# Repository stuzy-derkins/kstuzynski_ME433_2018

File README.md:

Kristen Stuzynski
4/8/2018
This repository has everything I'm learning in 433!
Adding another line to Sync...

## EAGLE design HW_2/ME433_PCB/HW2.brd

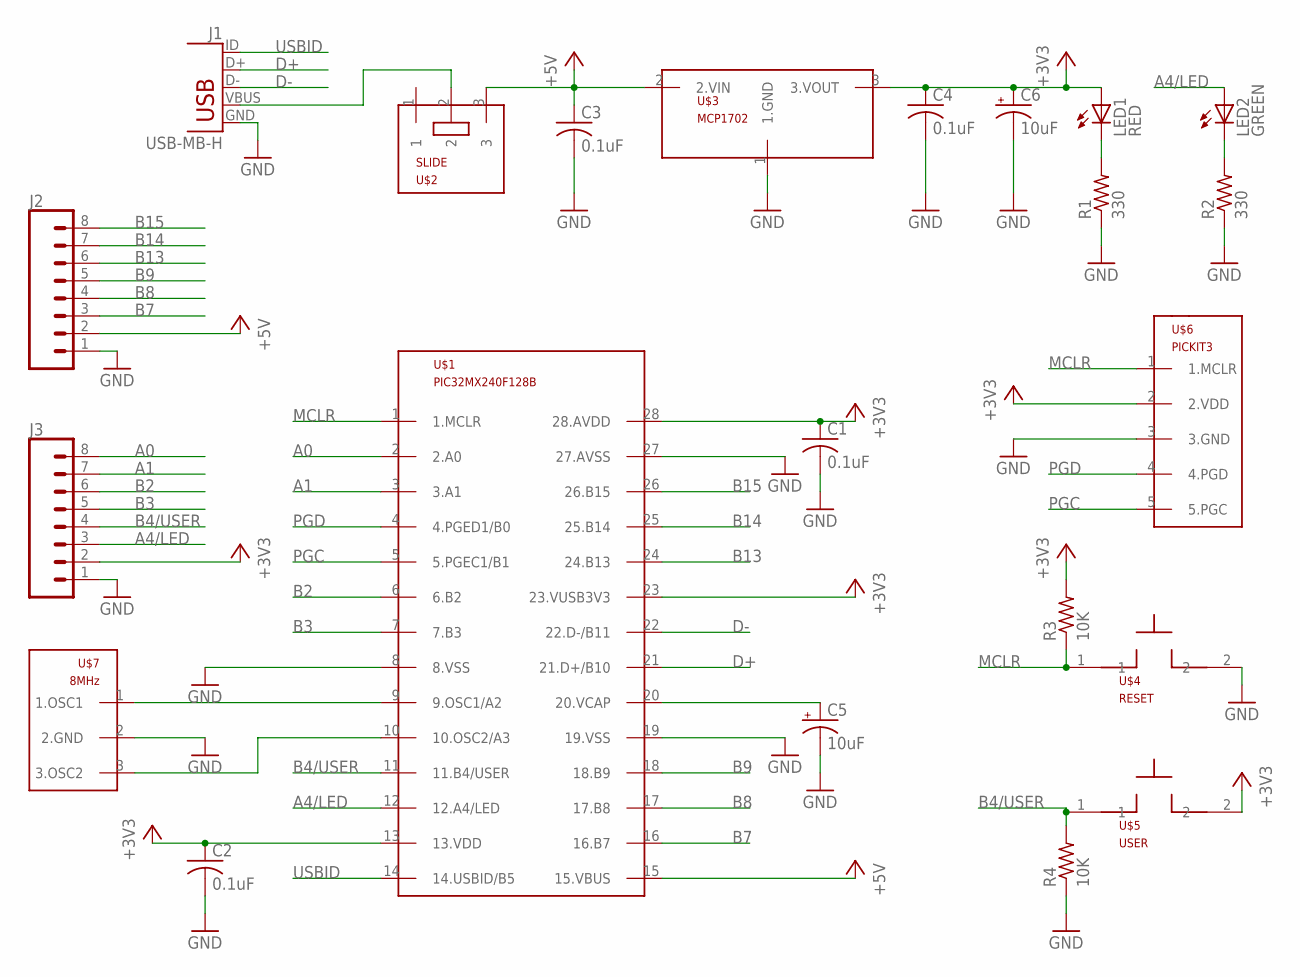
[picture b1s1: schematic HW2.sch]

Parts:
C1, C2, C3, C4: 0.1uF; C025-025X050
C5, C6: 10uF; B45181B
J1: USB-MB-H
J2, J3: CONN_08"; 1X08
LED1: RED; LED3MM
LED2: GREEN; LED3MM
R1, R2: 330; 0207/10
R3, R4: 10K; 0207/10
U$1: PIC32MX240F128B; DIL28-3
U$2: SLIDE
U$3: MCP1702; TO92
U$4: RESET; PUSHBUTTON
U$5: USER; PUSHBUTTON
U$6: PICKIT3; 1X05
U$7: 8MHz; OSC

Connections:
+3V3: C1.1, C2.1, C4.1, C6.+, J3.2, LED1.A, R3.2, U$1.13 (13.VDD), U$1.23 (23.VUSB3V3), U$1.28 (28.AVDD), U$3.3 (3.VOUT), U$5.2, U$6.2 (2.VDD)
+5V: C3.1, J2.2, U$1.15 (15.VBUS), U$2.3, U$3.2 (2.VIN)
A0: J3.8, U$1.2 (2.A0)
A1: J3.7, U$1.3 (3.A1)
A4/LED: J3.3, LED2.A, U$1.12 (12.A4/LED)
B2: J3.6, U$1.6 (6.B2)
B3: J3.5, U$1.7 (7.B3)
B4/USER: J3.4, R4.2, U$1.11 (11.B4/USER), U$5.1
B7: J2.3, U$1.16 (16.B7)
B8: J2.4, U$1.17 (17.B8)
B9: J2.5, U$1.18 (18.B9)
B13: J2.6, U$1.24 (24.B13)
B14: J2.7, U$1.25 (25.B14)
B15: J2.8, U$1.26 (26.B15)
D+: J1.D+, U$1.21 (21.D+/B10)
D-: J1.D-, U$1.22 (22.D-/B11)
GND: C1.2, C2.2, C3.2, C4.2, C5.-, C6.-, J1.GND, J2.1, J3.1, R1.1, R2.1, R4.1, U$1.8 (8.VSS), U$1.19 (19.VSS), U$1.27 (27.AVSS), U$3.1 (1.GND), U$4.2, U$6.3 (3.GND), U$7.2 (2.GND)
MCLR: R3.1, U$1.1 (1.MCLR), U$4.1, U$6.1 (1.MCLR)
unnamed: J1.VBUS, U$2.2
unnamed: LED1.K (C), R1.2
unnamed: U$1.9 (9.OSC1/A2), U$7.1 (1.OSC1)
unnamed: U$1.10 (10.OSC2/A3), U$7.3 (3.OSC2)
unnamed: C5.+, U$1.20 (20.VCAP)
unnamed: LED2.K (C), R2.2
PGC: U$1.5 (5.PGEC1/B1), U$6.5 (5.PGC)
PGD: U$1.4 (4.PGED1/B0), U$6.4 (4.PGD)
USBID: J1.ID, U$1.14 (14.USBID/B5)

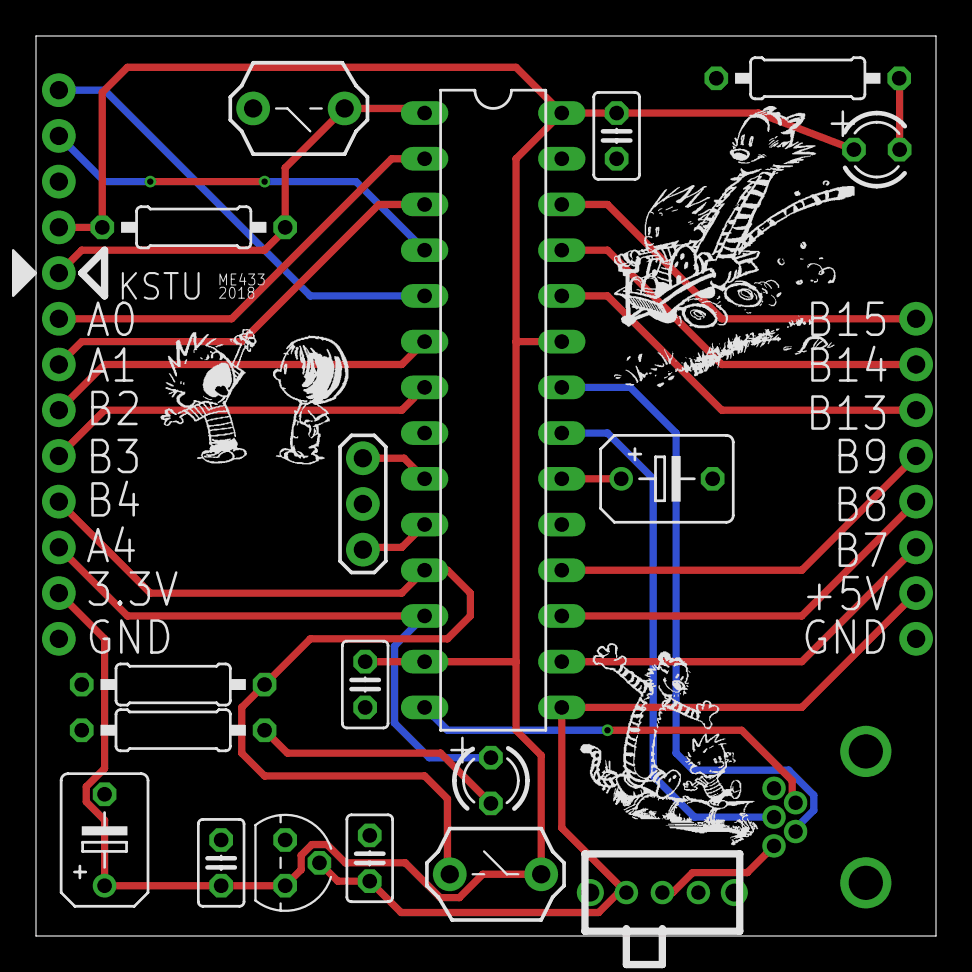
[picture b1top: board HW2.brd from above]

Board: 2 copper layers, 50.0 x 50.0 mm, 22 parts (0 on the bottom side), 27 nets.

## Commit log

2018-04-09 My first commit!
    woo!
2018-04-09 Sync
2018-04-09 HW1_pictures
    Circuit diagram, nScope oscillations, clean 3.3V, and final circuit.
2018-04-09 Created HW1 Project
2018-04-10 HW1 Final Commit
2018-04-11 HW1_Reorganized
2018-04-17 PCB
    schematics and board layout
2018-04-17 Gerber Files
2018-04-30 HW5(v2)
    added the 5Hz blinking LED on PIC to make sure code is still running
2018-05-17 HW12
